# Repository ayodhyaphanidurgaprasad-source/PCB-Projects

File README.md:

<div align="center" style="border: 2px solid #ccc; padding: 20px; border-radius: 12px; width: 80%; margin: auto; box-shadow: 0 0 10px rgba(0,0,0,0.15);">

  <h1 align="center" style="font-family: Arial; font-weight: 600; margin-top: 15px;">SURE ProEd (formerly SURE Trust) 
      </h1>
<h2 style="color: #2b6cb0; font-family: Arial;">Skill Upgradation for Rural youth Empowerment Trust</h2>
</div>

<hr style="border: 0; border-top: 1px solid #ccc; width: 80%;" />

<div style="padding: 20px; border: 2px solid #ddd; border-radius: 12px; width: 90%; margin: auto; background: #fafafa; font-family: Arial;">

<h2 style = "color:#333;"> student details </h2>
<div align = "left" style ="margin: 20px; font-size: 16px;">
    <p><strong>Name:</strong> A Phani durga prasad 
    <p><strong>Email ID:</strong> phanig6pcb@gmail.com  
    <p><strong>College Name:</strong> JNTUK clg of engineering 
    <p><strong>Branch/Specialization :</strong>  Electronics And Communication Engineering
    <p><strong>College ID:</strong> VVGV 
</div>

<hr style="border: 0; border-top: 1px solid #ccc; width: 80%;" />

<h2 style="color:#333;"> Course Details </h2>
<div align="left" style="margin: 20px; font-size: 16px;">
    <p><strong>Course Opted:</strong>  pcb designing </p>
    <p><strong>Instructor Name:</strong>paramaesh kumar </p>
</div>
<div align="left" style="margin: 20px; font-size: 16px;">
    <p><strong>Duration:</strong> 6 months </p>

<hr style="border: 0; border-top: 1px solid #ccc; width: 80%;" />

<h2 style="color:#333;"> Trainer Details </h2>
<div align="left" style="margin: 20px; font-size: 16px;">

<p><strong>Trainer Name:</strong> paramesh kumar</p>
<p><strong>Trainer Email ID:</strong> <!–– Add trainer email ––></p>
<p><strong>Trainer Designation:</strong> Hardware design engineer</p>

<hr style="border: 0; border-top: 1px solid #ccc; width: 80%;" />

## **Table of Contents**
- [Course Learning]( )
- [Projects Completed]( )
- [Project Introduction]()
- [Technologies Used]()
- [Roles and Responsibilities]()
- [Project Report] 
- [Learnings from LST & SST]
- [Community Services]
- [Certificate](#certificate)
- [Acknowledgments]()

<hr style="border: 0; border-top: 1px solid #ccc; width: 80%;" />

## Overall Learning 

> Through this project and my PCB Design internship, I gained 
practical knowledge of the complete PCB design process using KiCad 
I learned how to understand circuit requirements and develop a 
schematic by placing electronic components and creating the 
required electrical connections.   
I learned how to select suitable components and assign appropriate 
PCB footprints based on their package types and pin configurations. 
I also gained practical experience in transferring the schematic to the 
PCB Editor and developing a two-layer PCB layout.

<h2 style="color:#333;"> Projects Completed </h2>
<div align="left" style="margin: 20px; font-size: 16px;">

<p><strong><a href="#project1">Project 1:</a></strong> &lt;!USB TO ETHERCAT ADAPTER BOARD --&gt;</p>

<p><em>(You can add more projects as needed)</em></p>

</div>

<!-- Project 1 -->
<h3 id="project1">Project 1:USB TO ETHERCAT ADAPTER BOARD</h3>
<p>
  This project involved designing and developing a basic functional module using the core concepts taught in the course.
  It focused on understanding requirements, creating structured code, and implementing key features.
</p>
<p>
  <a href="https://drive.google.com/file/d/1WjPeQ4_ROtsQY1Z5-Qa-9GvYlF8fYWXm/view?usp=sharing" target="_blank"><strong>→ View Full Project Report</strong></a>
</p>

<hr style="height:1px; border-top:1px solid #ccc; width:80%;" />

## **References**

- [Wikipedia]## 

- [KiCad Documentation](https://docs.kicad.org/)
- [EtherCAT Technology Group](https://www.ethercat.org/)
- [USB Implementers Forum](https://www.usb.org/)
- Datasheets and application notes of the electronic components used in the project.

## **Learnings from LST and SST**

LST – Life Skills Training
Through LST sessions, I improved my self-confidence, time management, problem-solving, decision-making, teamwork, and positive attitude. These sessions helped me handle challenges and become more responsible in my professional life.
SST – Soft Skills Training
Through SST sessions, I improved my communication skills, English speaking, presentation skills, interpersonal skills, active listening, and interview skills. These sessions helped me communicate more confidently in the workplace.)
---

## **Community Services**

During my internship, I participated in community service activities that helped me develop social responsibility, teamwork, and a willingness to support others.

### **Activities Involved**

- **Tree Plantation Drive** – Participated in tree planting and contributed to environmental awareness.
- **Helping Elderly Citizens** – Assisted elderly people with simple daily activities.

### **Impact / Contribution**

- Helped create a supportive environment during the blood donation camp. <!-- add the location where you given -->
- Actively participated in promoting a greener and cleaner surroundings.
- Offered personal assistance to elder citizens, strengthening community bonds.
- Improved skills in communication, coordination, and social responsibility.

### **Photos**

<!-- add your photos below -->
<!-- change url below with your image urls (inside  src='')-->

- These are just placeholder (sample) images <!-- remove this line -->

<div align="center">
<img src=https://private-user-images.githubusercontent.com/234721419/650107349-2a947a05-9667-44bd-af80-8f347febeba1.jpeg?jwt=eyJ0eXAiOiJKV1QiLCJhbGciOiJIUzI1NiJ9.eyJpc3MiOiJnaXRodWIuY29tIiwiYXVkIjoicmF3LmdpdGh1YnVzZXJjb250ZW50LmNvbSIsImtleSI6ImtleTUiLCJleHAiOjE3ODkxMTg1NzcsIm5iZiI6MTc4OTExODI3NywicGF0aCI6Ii8yMzQ3MjE0MTkvNjUwMTA3MzQ5LTJhOTQ3YTA1LTk2NjctNDRiZC1hZjgwLThmMzQ3ZmViZWJhMS5qcGVnP1gtQW16LUFsZ29yaXRobT1BV1M0LUhNQUMtU0hBMjU2JlgtQW16LUNyZWRlbnRpYWw9QUtJQVZDT0RZTFNBNTNQUUs0WkElMkYyMDI2MDkxMSUyRnVzLWVhc3QtMSUyRnMzJTJGYXdzNF9yZXF1ZXN0JlgtQW16LURhdGU9MjAyNjA5MTFUMDkxNzU3WiZYLUFtei1FeHBpcmVzPTMwMCZYLUFtei1TaWduYXR1cmU9NmYxN2E2MjNjZmY2OWQzN2VlNGUwNzY3MzE4Yjk2YzJiNjQxNjRmNmU0OTk0OTRkM2MwNjdmNDdjODU0NjBlNyZYLUFtei1TaWduZWRIZWFkZXJzPWhvc3QmcmVzcG9uc2UtY29udGVudC10eXBlPWltYWdlJTJGanBlZyJ9.VLdheQatjy0igjPNyJnIaTH-NHupB-m9WgW001OAxWY alt="Community Service Photo 1" width="30%">
<img src=https://private-user-images.githubusercontent.com/234721419/650109799-44141f3e-feb9-4ebb-92b9-c4be660c0f7b.jpeg?jwt=eyJ0eXAiOiJKV1QiLCJhbGciOiJIUzI1NiJ9.eyJpc3MiOiJnaXRodWIuY29tIiwiYXVkIjoicmF3LmdpdGh1YnVzZXJjb250ZW50LmNvbSIsImtleSI6ImtleTUiLCJleHAiOjE3ODkxMTg4NjEsIm5iZiI6MTc4OTExODU2MSwicGF0aCI6Ii8yMzQ3MjE0MTkvNjUwMTA5Nzk5LTQ0MTQxZjNlLWZlYjktNGViYi05MmI5LWM0YmU2NjBjMGY3Yi5qcGVnP1gtQW16LUFsZ29yaXRobT1BV1M0LUhNQUMtU0hBMjU2JlgtQW16LUNyZWRlbnRpYWw9QUtJQVZDT0RZTFNBNTNQUUs0WkElMkYyMDI2MDkxMSUyRnVzLWVhc3QtMSUyRnMzJTJGYXdzNF9yZXF1ZXN0JlgtQW16LURhdGU9MjAyNjA5MTFUMDkyMjQxWiZYLUFtei1FeHBpcmVzPTMwMCZYLUFtei1TaWduYXR1cmU9NTBlNDBjOTVjOTU1NTI2ODhhZjI5YTRhNDFmZDZhY2RkM2ZlMmQ5OTU3NDM0N2MyZjA5MzQwYWFjNmVmNWY0YiZYLUFtei1TaWduZWRIZWFkZXJzPWhvc3QmcmVzcG9uc2UtY29udGVudC10eXBlPWltYWdlJTJGanBlZyJ9.ohQwmAaQb4F6nk6vHhhchPrzfxOLnZUSM9fA1cL0Vic alt="Community Service Photo 2" width="30%">

## **Certificate**

The internship certificate serves as an official acknowledgment of the successful completion of my training period. It will be issued by the organization upon fulfilling all required tasks and meeting the performance expectations of the program. The certificate validates the skills, experience, and contributions made during the internship.

<!-- add your certificate image url below (inside src='')-->

---

## **Acknowledgments**

sincerely thank SURE Trust  for providing me with the opportunity to complete my internship in PCB Designing.
I am grateful to my trainers and mentors for their valuable guidance and support throughout the internship. I also thank the LST and SST trainers for helping me improve my life skills, communication, confidence, and professional skills.

- [Prof. Radhakumari Challa](https://www.linkedin.com/in/prof-radhakumari-challa-a3850219b) , Executive Director and Founder - [SURE Trust](https://www.suretrustforruralyouth.com/)

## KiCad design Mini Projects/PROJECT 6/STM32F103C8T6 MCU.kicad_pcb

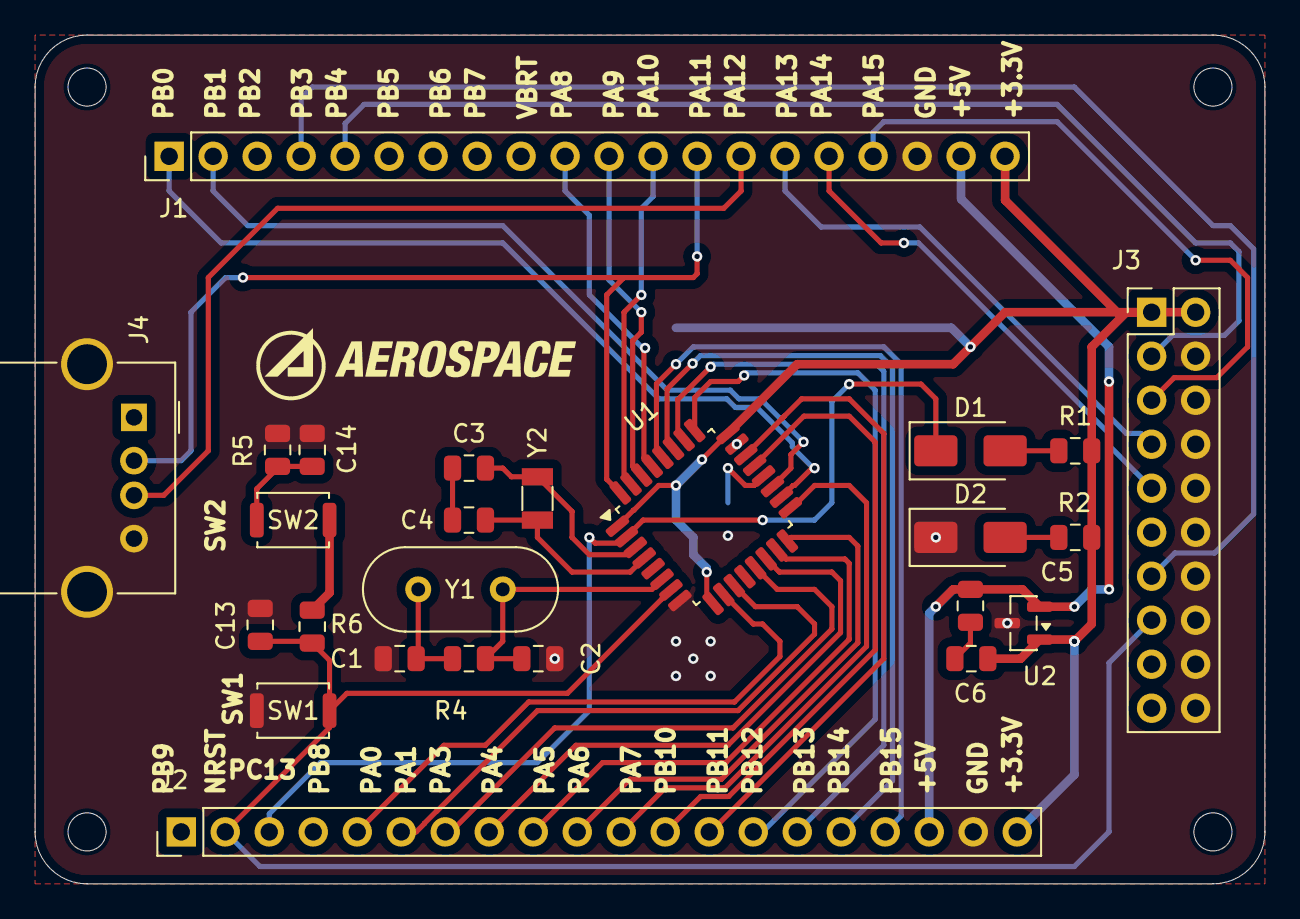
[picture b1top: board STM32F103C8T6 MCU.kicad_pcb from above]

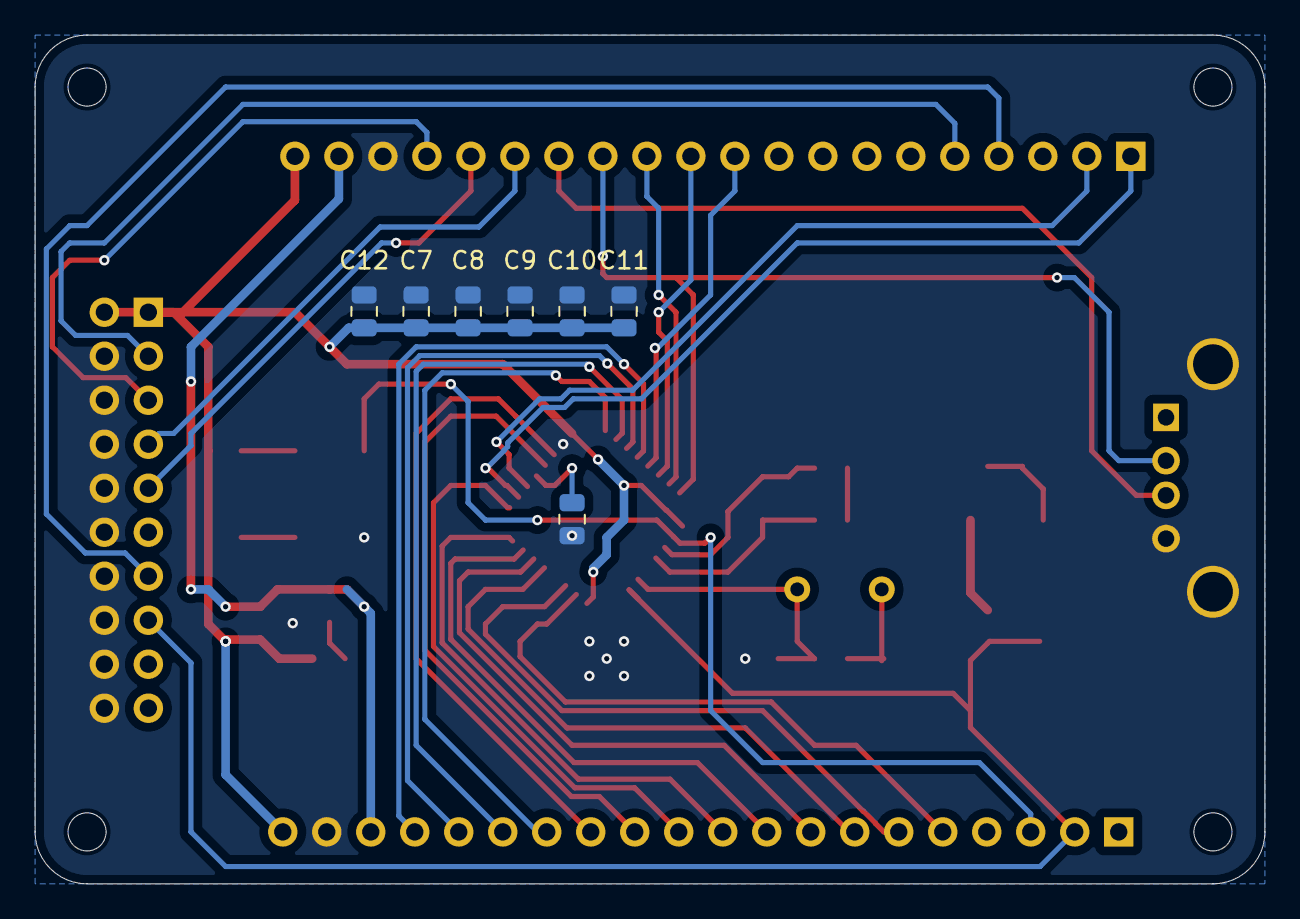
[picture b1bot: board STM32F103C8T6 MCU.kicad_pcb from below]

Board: 2 copper layers, 71.0 x 49.0 mm, 36 parts (7 on the bottom side), 41 nets.

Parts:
C1, C2: 22pf; C_0805_2012Metric
C3, C4: 8pf; C_0805_2012Metric
C5: 0.47uf; C_0805_2012Metric
C6: 47uf; C_0805_2012Metric
C7, C13, C14: 100nf; C_0805_2012Metric
C8: 10nf; C_0805_2012Metric
C9, C10, C11: 100pf; C_0805_2012Metric
C12: 1uf; C_0805_2012Metric
D1, D2: LED; D_SMA
H1, H2, H3, H4: MountingHole; MountingHole_2.2mm_M2
J1, J2: Conn_01x20; PinHeader_1x20_P2.54mm_Vertical
J3: Conn_02x10_Odd_Even; PinHeader_2x10_P2.54mm_Vertical
J4: USB_B; USB_A_Molex_67643_Horizontal
R1, R2: 1K; C_0805_2012Metric
R3, R6: 10K; C_0805_2012Metric
R4: 1M; C_0805_2012Metric
R5: 100K; C_0805_2012Metric
SW1, SW2: SW_DPST_x2; SW_Push_SPST_NO_Alps_SKRK
U1: STM32F103C8Tx; TQFP-32_7x7mm_P0.8mm
U2: LM3480-3.3; SOT-23
Y1: 8mhz; Crystal_HC49-4H_Vertical
Y2: 32.768khz; Crystal_SMD_3215-2Pin_3.2x1.5mm

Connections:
+3.3V: C6.1, C7.1, C8.1, C9.1, C10.1, C11.1, C12.1, J1.20, J2.20, J3.1, J3.2, R1.1, R2.1, U1.1 (VBAT), U1.9 (VDDA), U1.24 (VDD), U2.1 (VO)
+3.3v: R6.1, SW2.1 (A)
+5V: C5.1, J1.19, J2.18, U2.2 (VI)
BOOTO: C14.1, R5.1, SW2.2 (B)
GND: C1.1, C2.1, C7.2, C8.2, C9.2, C10.2, C11.2, C12.2, C13.2, C14.2, D2.1 (K), J1.18, J2.19, J3.4, J3.6, J3.8, J3.10, J3.12, J3.14, J3.16, J3.18, J3.20, J4.4 (GND), J4.5 (Shield), R3.1, R5.2, SW1.1 (A), U1.8 (VSSA), U1.23 (VSS), U2.3 (GND)
NRST: C13.1, J2.2, J3.15, R6.2, SW1.2 (B), U1.7 (NRST)
unnamed: C3.1, C4.1
unnamed: C5.2, C6.2
unnamed: D1.2 (A), R1.2
unnamed: D2.2 (A), R2.2
unnamed: R3.2, U1.20 (PB2)
PA1: J2.6, U1.11 (PA1)
PA3: J2.7, U1.13 (PA3)
PA4: J2.8, U1.14 (PA4)
PA5: J2.9, U1.15 (PA5)
PA6: J2.10, U1.16 (PA6)
PA7: J2.11, U1.17 (PA7)
PA8: J1.10, U1.29 (PA8)
PA9: J1.11, U1.30 (PA9)
PA10: J1.12, U1.31 (PA10)
PA11: J1.13, J4.2 (D-), U1.32 (PA11)
PA12: J1.14, J4.3 (D+)
PA13: J1.15, J3.7
PA14: J1.16, J3.9
PA15: J1.17, J3.5
PAO: J2.5, U1.10 (PA0)
PB0: J1.1, U1.18 (PB0)
PB1: J1.2, U1.19 (PB1)
PB3: J1.4, J3.13
PB4: J1.5, J3.3
PB10: J2.12, U1.21 (PB10)
PB11: J2.13, U1.22 (PB11)
PB12: J2.14, U1.25 (PB12)
PB13: J2.15, U1.26 (PB13)
PB14: J2.16, U1.27 (PB14)
PB15: J2.17, U1.28 (PB15)
PC13: D1.1 (K), J2.3, U1.2 (PC13)
PC14: C3.2, U1.3 (PC14), Y2.2
PC15: C4.2, U1.4 (PC15), Y2.1
PD1: C2.2, R4.2, U1.6 (PD1), Y1.1
PDO: C1.2, R4.1, Y1.2

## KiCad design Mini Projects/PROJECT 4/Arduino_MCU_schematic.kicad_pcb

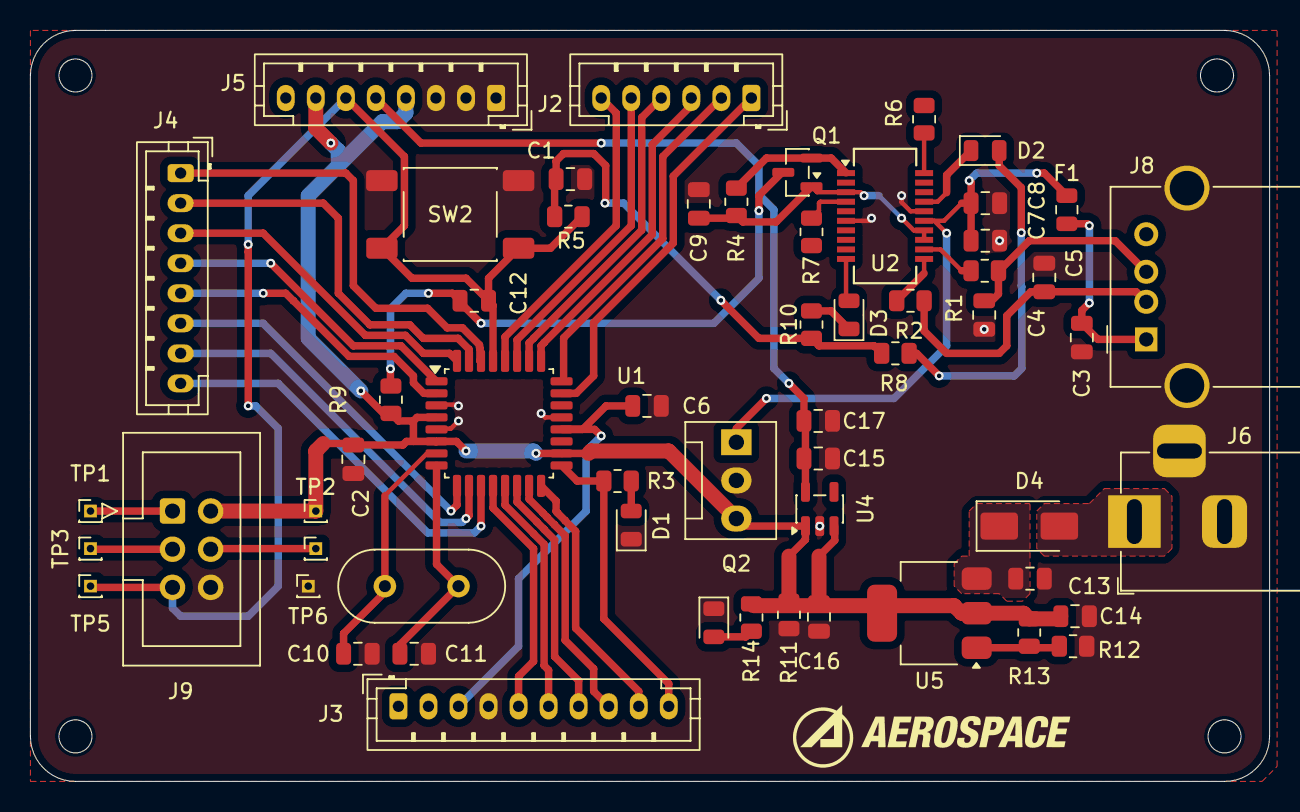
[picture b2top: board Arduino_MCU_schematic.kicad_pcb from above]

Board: 2 copper layers, 82.5 x 50.0 mm, 62 parts (0 on the bottom side), 51 nets.

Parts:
C1, C3, C6, C7: 0.1uf; C_0805_2012Metric
C2, C9, C10, C11, C12, C16: 0.1UF; C_0805_2012Metric
C4, C5: 47pf; C_0805_2012Metric
C8: 10uf; C_0805_2012Metric
C13, C14: 47UF; C_0805_2012Metric
C15: 1.0UF; C_0805_2012Metric
C17: 10UF; C_0805_2012Metric
D1: 10UF; LED_0805_2012Metric
D2: Yellow; LED_0805_2012Metric
D3: Red; LED_0805_2012Metric
D4: MBRA340; D_SMA
F1: 6v/0.5A; Fuse_0805_2012Metric
GREEN1: LED; LED_0805_2012Metric
H1, H2, H3, H4: MountingHole; MountingHole_2.2mm_M2
J2: Conn_01x06; JST_PH_B6B-PH-K_1x06_P2.00mm_Vertical
J3: Conn_01x10; JST_PH_B10B-PH-K_1x10_P2.00mm_Vertical
J4, J5: Conn_01x08; JST_PH_B8B-PH-K_1x08_P2.00mm_Vertical
J6: Barrel_Jack_Switch_Pin3Ring; BarrelJack_Horizontal
J8: USB_B_Micro; USB_A_Molex_67643_Horizontal
J9: AVR-ISP-6; IDC-Header_2x03_P2.54mm_Vertical
Q1: 2N7002; SOT-23
Q2: PMOS; FanPinHeader_1x03_P2.54mm_Vertical
R1, R2: 27; R_0805_2012Metric
R3, R6, R7, R8, R10: 1K; R_0805_2012Metric
R4, R9, R11: 10K; R_0805_2012Metric
R5: 1k; R_0805_2012Metric
R12: 715; R_0805_2012Metric
R13: 240; R_0805_2012Metric
R14: 4.7K; R_0805_2012Metric
SW2: SW_Push; SW_Push_1P1T_NO_E-Switch_TL3301NxxxxxG
TP1, TP2, TP3, TP4, TP5, TP6: TestPoint; PinHeader_1x01_P1.00mm_Vertical
U1: ATmega328P-A; TQFP-32_7x7mm_P0.8mm
U2: FT231XS; SSOP-20_3.9x8.7mm_P0.635mm
U4: MIC5205-2.5YM5; SOT-23-5
U5: AMS1117; SOT-223-3_TabPin2
Y1(16MHz)1: Crystal; Crystal_HC18-U_Vertical

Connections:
3.3V_F: C9.1, Q1.1 (G), R4.1, U2.3 (VCCIO), U2.13 (3V3OUT), U2.14 (~RESET)
+3.3V: C15.1, C17.1, J5.5, U4.5 (OUT)
+5V: C2.1, C14.1, C16.1, J5.4, J5.7, J9.2 (VCC), Q2.3 (S), R9.1, R11.1, R13.1, R14.1, TP2.1, U1.4 (VCC), U1.6 (VCC), U1.18 (AVCC), U4.1 (IN), U4.3 (EN), U5.2 (VO)
+5v: C1.1, R5.1, R8.1, R10.1
AREF: C6.2, J3.3, U1.20 (AREF)
DTR: C12.1, Q1.3 (D), R9.2
GND: C1.2, C2.2, C3.2, C4.2, C5.2, C6.1, C7.2, C8.2, C9.2, C10.2, C11.2, C13.2, C14.2, C15.2, C16.2, C17.2, D1.1 (K), GREEN1.1 (K), J3.4, J5.1, J5.2, J5.3, J6.2, J6.3, J8.5 (GND), J9.6 (GND), Q2.2 (G), R11.2, R12.2, SW2.2, TP6.1, U1.3 (GND), U1.5 (GND), U1.21 (GND), U2.6 (GND), U2.16 (GND), U4.2 (GND)
MISO: J9.1 (MISO), TP1.1
MOSI: J9.4 (MOSI), TP4.1
unnamed: D1.2 (A), R3.2
unnamed: D2.2 (A), R8.2
unnamed: D2.1 (K), U2.17 (CBUS1)
unnamed: D3.2 (A), U2.10 (CBUS2)
unnamed: D3.1 (K), R10.2
unnamed: D4.2 (A), J6.1
unnamed: GREEN1.2 (A), R14.2
unnamed: J2.1, U1.23 (PC0)
unnamed: J2.2, U1.24 (PC1)
unnamed: J2.3, U1.25 (PC2)
unnamed: J2.4, U1.26 (PC3)
unnamed: J2.5, U1.27 (PC4)
unnamed: J2.6, U1.28 (PC5)
unnamed: J3.5, U1.12 (PB0)
unnamed: J3.6, U1.13 (PB1)
unnamed: J3.7, U1.14 (PB2)
unnamed: J3.8, U1.15 (PB3)
unnamed: J3.9, U1.16 (PB4)
unnamed: J3.10, R3.1, U1.17 (PB5)
unnamed: J4.1, U1.30 (PD0)
unnamed: J4.2, U1.31 (PD1)
unnamed: J4.3, U1.32 (PD2)
unnamed: J4.4, U1.1 (PD3)
unnamed: J4.5, U1.2 (PD4)
unnamed: J4.6, U1.9 (PD5)
unnamed: J4.7, U1.10 (PD6)
unnamed: J4.8, U1.11 (PD7)
unnamed: C4.1, J8.3 (D+), R1.1
unnamed: C5.1, J8.2 (D-), R2.1
unnamed: C3.1, F1.1, J8.1 (VBUS)
unnamed: Q1.2 (S), R4.2, U2.1 (~DTR)
unnamed: C10.1, U1.7 (XTAL1/PB6), Y1(16MHz)1.2
unnamed: C11.1, U1.8 (XTAL2/PB7), Y1(16MHz)1.1
unnamed: R7.1, U2.4 (RXD)
unnamed: R6.1, U2.20 (TXD)
unnamed: R1.2, U2.12 (USBDM)
unnamed: R2.2, U2.11 (USBDP)
unnamed: R12.1, R13.2, U5.1 (ADJ)
RESET: C12.2, J5.6, J9.5 (~RST), R5.2, SW2.1, TP5.1, U1.29 (~RESET/PC6)
SCK: J9.3 (SCK), TP3.1
USBVCC: C7.1, C8.1, F1.2, Q2.1 (D), U2.15 (VCC)
VIN: C13.1, D4.1 (K), U5.3 (VI)

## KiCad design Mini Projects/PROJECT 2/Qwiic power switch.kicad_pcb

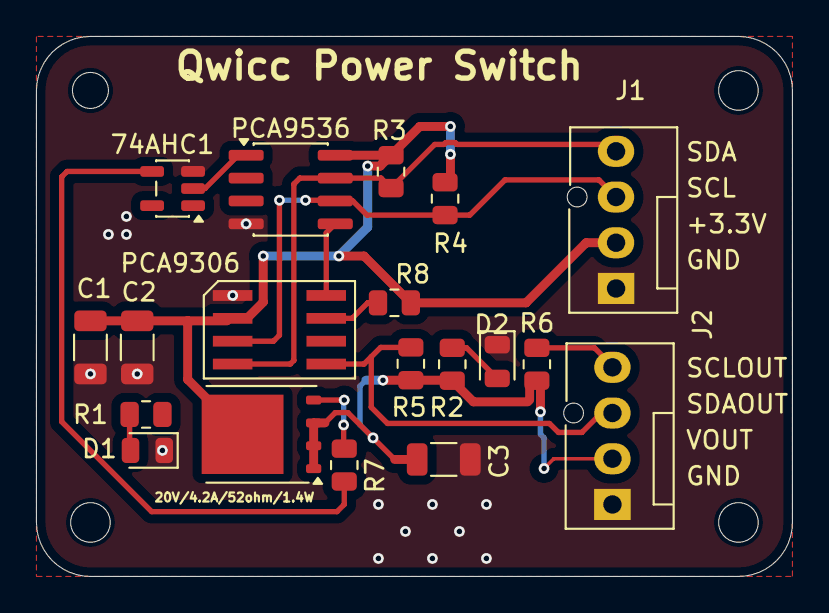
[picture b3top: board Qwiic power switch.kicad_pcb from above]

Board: 2 copper layers, 42.0 x 30.0 mm, 23 parts (0 on the bottom side), 14 nets.

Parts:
20V/4.2A/52ohm/1.4W: 20v/4.2A/52ohm/1.4w; TDSON-8-1
74AHC1: 74AHC1GU04; SOT-23-5
C1: 10UF/0805; C_1206_3216Metric
C2, C3: 0.1UF/0805; C_1206_3216Metric
D1: RED; LED_0805_2012Metric
D2: GREEN; LED_0805_2012Metric
H1, H2, H3, H4: MountingHole; MountingHole_2.2mm_M2
J1, J2: Conn_01x04_Pin; FanPinHeader_1x04_P2.54mm_Vertical
PCA9306: SOIC-8
PCA9536: PCA9536D; SOIC-8_3.9x4.9mm_P1.27mm
R1: 11/0805; R_0805_2012Metric
R2: 470/0805; R_0805_2012Metric
R3, R4, R5, R6: 2.2K/0805; R_0805_2012Metric
R7: 1K/0805; R_0805_2012Metric
R8: 200K/0805; R_0805_2012Metric

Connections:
+3.3V: 20V/4.2A/52ohm/1.4W.5 (D), C1.1, C2.1, J1.2, PCA9306.2 (Vref_1), PCA9536.8 (VDD), R3.1, R4.1, R8.1
GND: 74AHC1.3 (GND), C1.2, C2.2, C3.2, D1.1 (K), D2.1 (K), J1.1, J2.1, PCA9306.1 (GND), PCA9536.4 (VSS)
GPIO0: 74AHC1.2, PCA9536.1 (IO0)
GPIO3: PCA9306.8 (EN), PCA9536.5 (IO3)
unnamed: D1.2 (A), R1.2
unnamed: D2.2 (A), R2.2
unnamed: PCA9306.7 (Vref_2), R8.2
unnamed: 20V/4.2A/52ohm/1.4W.4 (G), R7.2
unnamed: 74AHC1.4, R7.1
SCL: J1.3, PCA9306.3 (scl_1), PCA9536.6 (SCL), R4.2
SCL_OUT: J2.4, R6.2
SDA: J1.4, PCA9306.4 (sda_1), PCA9536.7 (SDA), R3.2
SDA_OUT: J2.3, PCA9306.5 (sda_2), R5.2
VOUT: 20V/4.2A/52ohm/1.4W.1 (S), 20V/4.2A/52ohm/1.4W.2 (S), 20V/4.2A/52ohm/1.4W.3 (S), C3.1, J2.2, R2.1, R5.1, R6.1

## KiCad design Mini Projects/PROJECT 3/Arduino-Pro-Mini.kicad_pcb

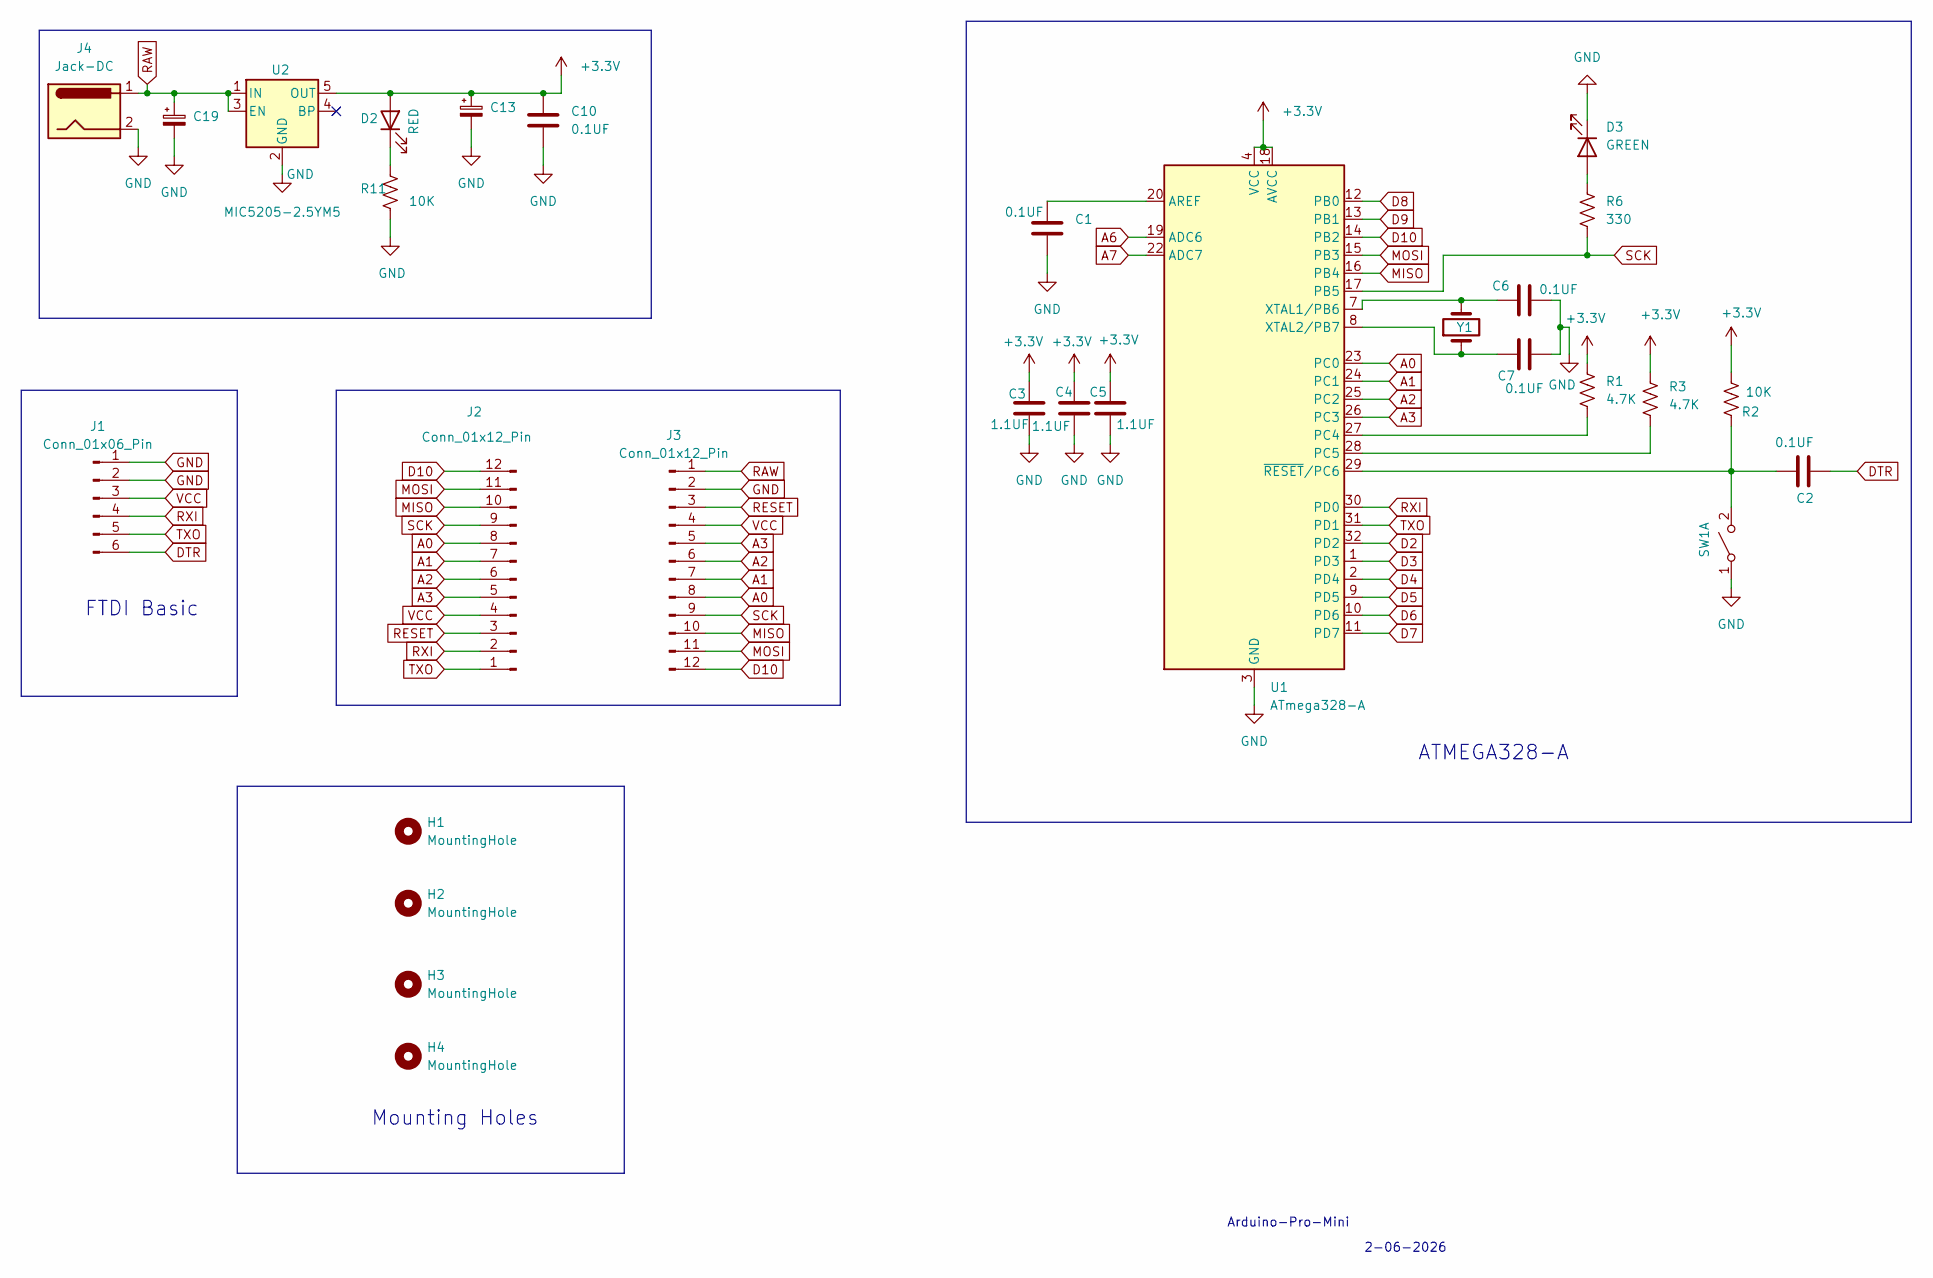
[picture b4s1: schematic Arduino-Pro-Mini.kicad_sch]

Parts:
C1, C2, C6, C7, C10: 0.1UF; C_0805_2012Metric
C3, C4, C5: 1.1UF; C_0805_2012Metric
C13, C19: C_Polarized_Small; CP_Elec_3x5.3
D2: RED; LED_0805_2012Metric
D3: GREEN; LED_0805_2012Metric
H1, H2, H3, H4: MountingHole; MountingHole_2.2mm_M2
J1: Conn_01x06_Pin; PinHeader_1x06_P1.27mm_Vertical
J2, J3: Conn_01x12_Pin; PinSocket_1x12_P1.27mm_Vertical
J4: Jack-DC; BarrelJack_Horizontal
R1, R3: 4.7K; R_0805_2012Metric
R2, R11: 10K; R_0805_2012Metric
R6: 330; R_0805_2012Metric
SW1: SW_DPST_x2; LED_RGB_Wuerth_150080M153000
U1: ATmega328-A; TQFP-32_7x7mm_P0.8mm
U2: MIC5205-2.5YM5; SOT-23-5
Y1: Crystal; Crystal_HC52-U_Vertical

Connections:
+3.3V: C3.1, C4.1, C5.1, C10.1, C13.1, D2.2 (A), R1.1, R2.2, R3.1, U1.4 (VCC), U1.6 (VCC), U1.18 (AVCC), U2.5 (OUT)
A0: J2.8, J3.8, U1.23 (PC0)
A1: J2.7, J3.7, U1.24 (PC1)
A2: J2.6, J3.6, U1.25 (PC2)
A3: J2.5, J3.5, U1.26 (PC3)
A6: U1.19 (ADC6)
A7: U1.22 (ADC7)
D2: U1.32 (PD2)
D3: U1.1 (PD3)
D4: U1.2 (PD4)
D5: U1.9 (PD5)
D6: U1.10 (PD6)
D7: U1.11 (PD7)
D8: U1.12 (PB0)
D9: U1.13 (PB1)
D10: J2.12, J3.12, U1.14 (PB2)
DTR: C2.1, J1.6
GND: C1.2, C3.2, C4.2, C5.2, C6.1, C7.2, C10.2, C13.2, C19.2, D3.1 (K), J1.1, J1.2, J3.2, J4.2, R11.2, SW1.1 (A), U1.3 (GND), U1.5 (GND), U1.21 (GND), U2.2 (GND)
MISO: J2.10, J3.10, U1.16 (PB4)
MOSI: J2.11, J3.11, U1.15 (PB3)
unnamed: D2.1 (K), R11.1
unnamed: D3.2 (A), R6.1
unnamed: C2.2, R2.1, SW1.2 (B), U1.29 (~RESET/PC6)
unnamed: C1.1, U1.20 (AREF)
unnamed: R1.2, U1.27 (PC4)
unnamed: R3.2, U1.28 (PC5)
unnamed: C6.2, U1.7 (XTAL1/PB6), Y1.2
unnamed: C7.1, U1.8 (XTAL2/PB7), Y1.1
RAW: C19.1, J3.1, J4.1, U2.1 (IN), U2.3 (EN)
RESET: J2.3, J3.3
RXI: J1.4, J2.2, U1.30 (PD0)
SCK: J2.9, J3.9, R6.2, U1.17 (PB5)
TXO: J1.5, J2.1, U1.31 (PD1)
VCC: J1.3, J2.4, J3.4

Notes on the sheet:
Mounting Holes
ATMEGA328-A
Arduino-Pro-Mini
2-06-2026
FTDI Basic

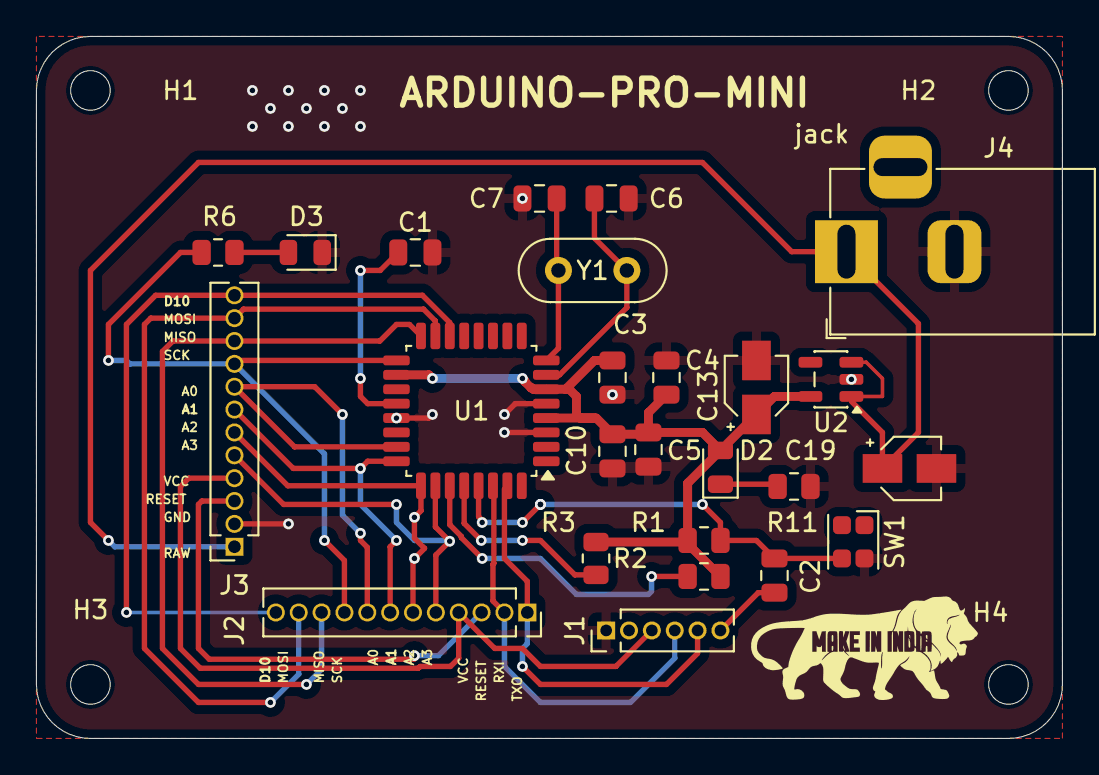
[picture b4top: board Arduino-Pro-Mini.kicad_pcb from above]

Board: 2 copper layers, 57.0 x 39.0 mm, 29 parts (0 on the bottom side), 24 nets.

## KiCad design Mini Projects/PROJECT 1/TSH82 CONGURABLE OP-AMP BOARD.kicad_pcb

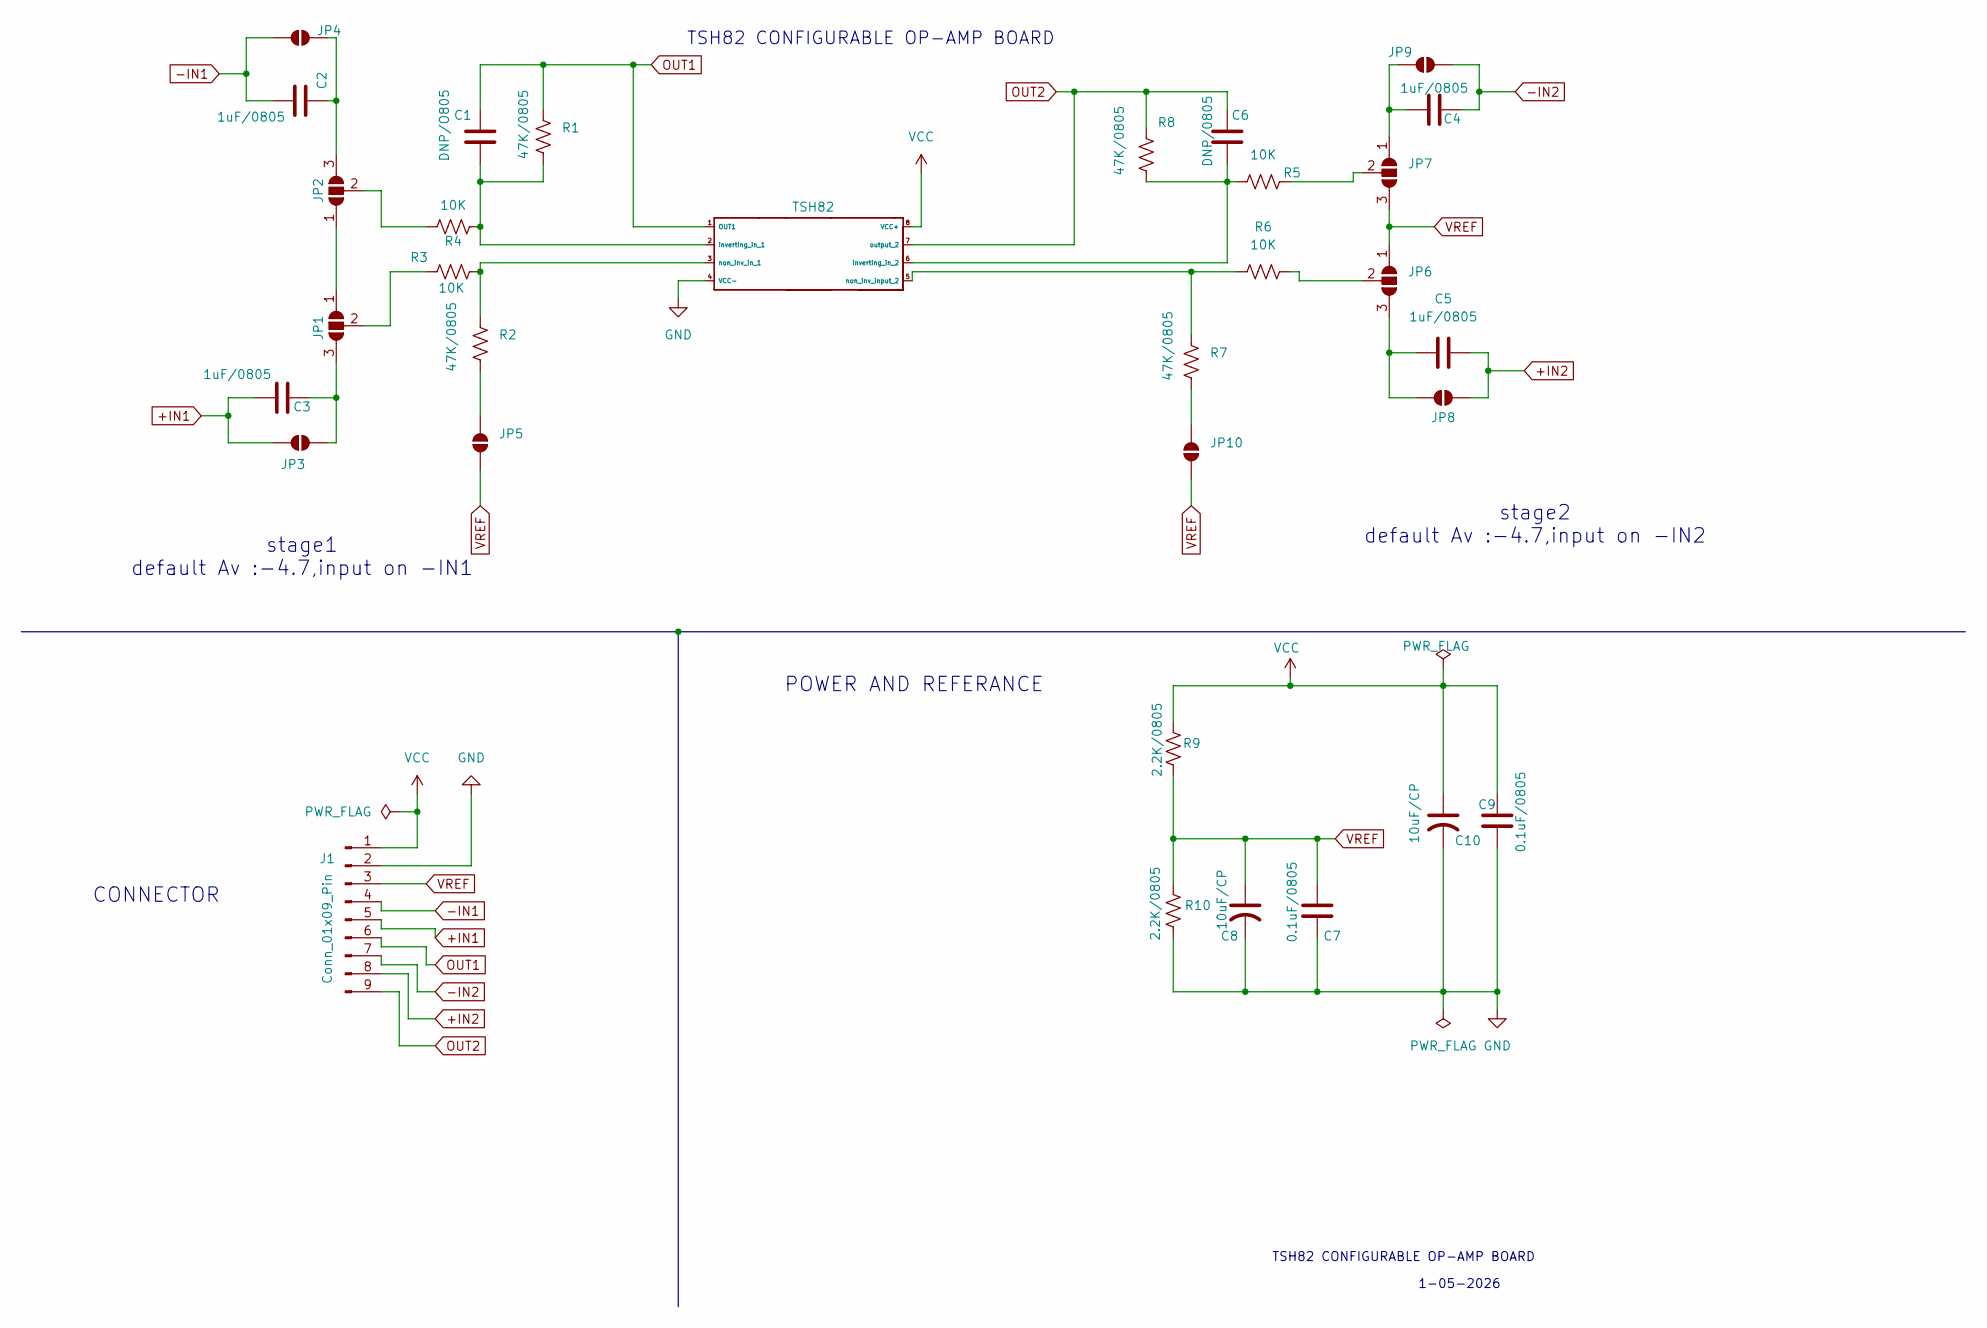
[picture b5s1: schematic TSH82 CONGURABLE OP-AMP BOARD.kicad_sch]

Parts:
C1: DNP/O805; C_1206_3216Metric
C2, C3, C4, C5: 1uF/0805; C_1206_3216Metric
C6: DNP/0805; C_1206_3216Metric
C7, C9: 0.1uF/0805; C_1206_3216Metric
C8, C10: 10uF/CP; C_1206_3216Metric
J1: Conn_01x09_Pin; PinHeader_1x09_P1.27mm_Vertical
JP1, JP2, JP6, JP7: SolderJumper_3_Open; SolderJumper-3_P1.3mm_Open_Pad1.0x1.5mm
JP3, JP4, JP5, JP8, JP9, JP10: SolderJumper_2_Open; SolderJumper-2_P1.3mm_Open_Pad1.0x1.5mm
R1, R2, R7, R8: 47K/0805; R_0805_2012Metric
R3, R4, R5, R6: 10K; R_0805_2012Metric
R9, R10: 2.2K/0805; R_0805_2012Metric
TSH82: SOIC-8

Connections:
+IN1: C3.1, J1.5, JP3.1 (A)
+IN2: C5.2, J1.8, JP8.2 (B)
-IN1: C2.1, J1.4, JP4.1 (A)
-IN2: C4.2, J1.7, JP9.2 (B)
GND: C7.2, C8.2, C9.2, C10.2, J1.2, R10.2, TSH82.4 (VCC-)
unnamed: JP1.1 (A), JP2.1 (A)
unnamed: C3.2, JP1.3 (B), JP3.2 (B)
unnamed: JP1.2 (C), R3.1
unnamed: C2.2, JP2.3 (B), JP4.2 (B)
unnamed: JP2.2 (C), R4.1
unnamed: JP5.2 (B), R2.2
unnamed: C5.1, JP6.3 (B), JP8.1 (A)
unnamed: JP6.2 (C), R6.2
unnamed: C4.1, JP7.1 (A), JP9.1 (A)
unnamed: JP7.2 (C), R5.2
unnamed: JP10.2 (B), R7.2
unnamed: C1.2, R1.2, R4.2, TSH82.2 (inverting_in_1)
unnamed: C6.2, R5.1, R8.2, TSH82.6 (inverting_in_2)
unnamed: R2.1, R3.2, TSH82.3 (non_inv_in_1)
unnamed: R6.1, R7.1, TSH82.5 (non_inv_input_2)
OUT1: C1.1, J1.6, R1.1, TSH82.1 (OUT1)
OUT2: C6.1, J1.9, R8.1, TSH82.7 (output_2)
VCC: C9.1, C10.1, J1.1, R9.1, TSH82.8 (VCC+)
VREF: C7.1, C8.1, J1.3, JP5.1 (A), JP6.1 (A), JP7.3 (B), JP10.1 (A), R9.2, R10.1

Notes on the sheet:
CONNECTOR
stage2 default Av :-4.7,input on -IN2
stage1 default Av :-4.7,input on -IN1
TSH82 CONFIGURABLE OP-AMP BOARD
1-05-2026
POWER AND REFERANCE

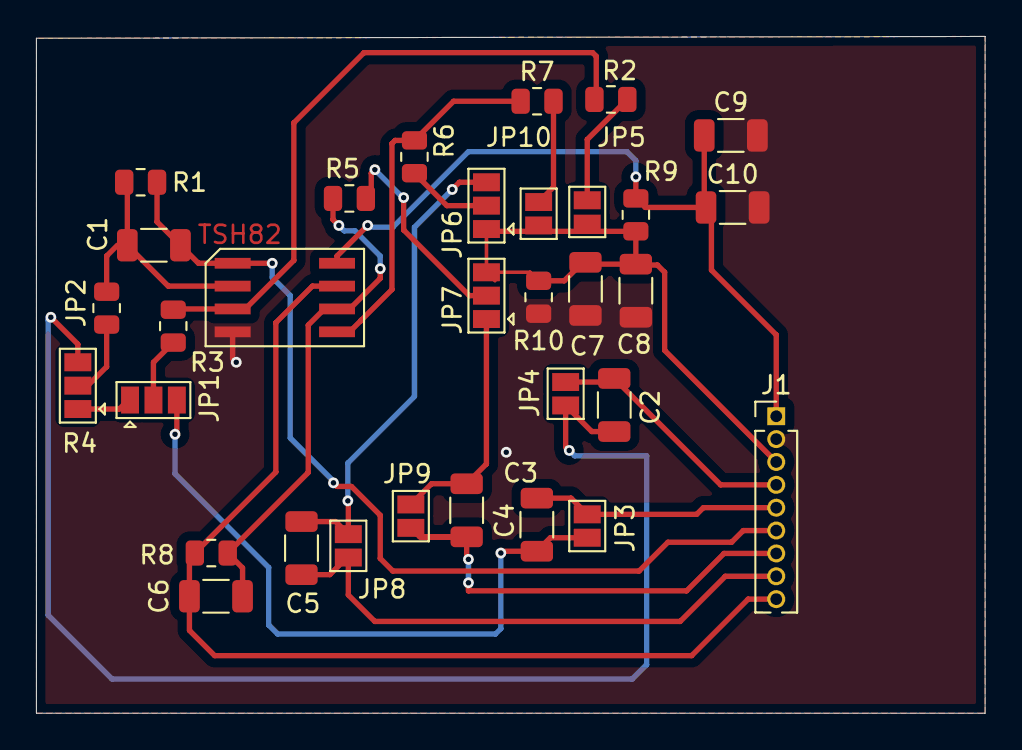
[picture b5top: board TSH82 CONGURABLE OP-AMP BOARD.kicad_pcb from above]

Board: 2 copper layers, 52.7 x 37.6 mm, 32 parts (0 on the bottom side), 24 nets.
